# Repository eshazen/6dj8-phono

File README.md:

# 6dj8 phono preamp

This is a project to build a 6DJ8 (ECC88) tube phono stage as inspired by RJM audio (phonoclone.com).  The 6DJ8 seems to be out of production, but still readily available.

## Power board:

IEC power input, fuse, switch, neon as in https://github.com/eshazen/6cy7-amp.  PT, chokes mounted on PCB also.  Single noval socket for 6CA4 (ceramic).  Two B+ outputs for two channels.

## Channel board (2):

Single tube (6DJ8/ECC88) per channel.  RCA inputs and outputs, plus GND.  Power connector.

## Progress

*2021-05-01* - Schematics done for PS and amp.  Footprints done and DigiKey numbers on amp schematic, starting placement

*2021-05-02* - Finished amp layout, placement for PS.  Resized boards so the stack of 3 has the same footprint as the 6CY7 amp (7.5 x 15").

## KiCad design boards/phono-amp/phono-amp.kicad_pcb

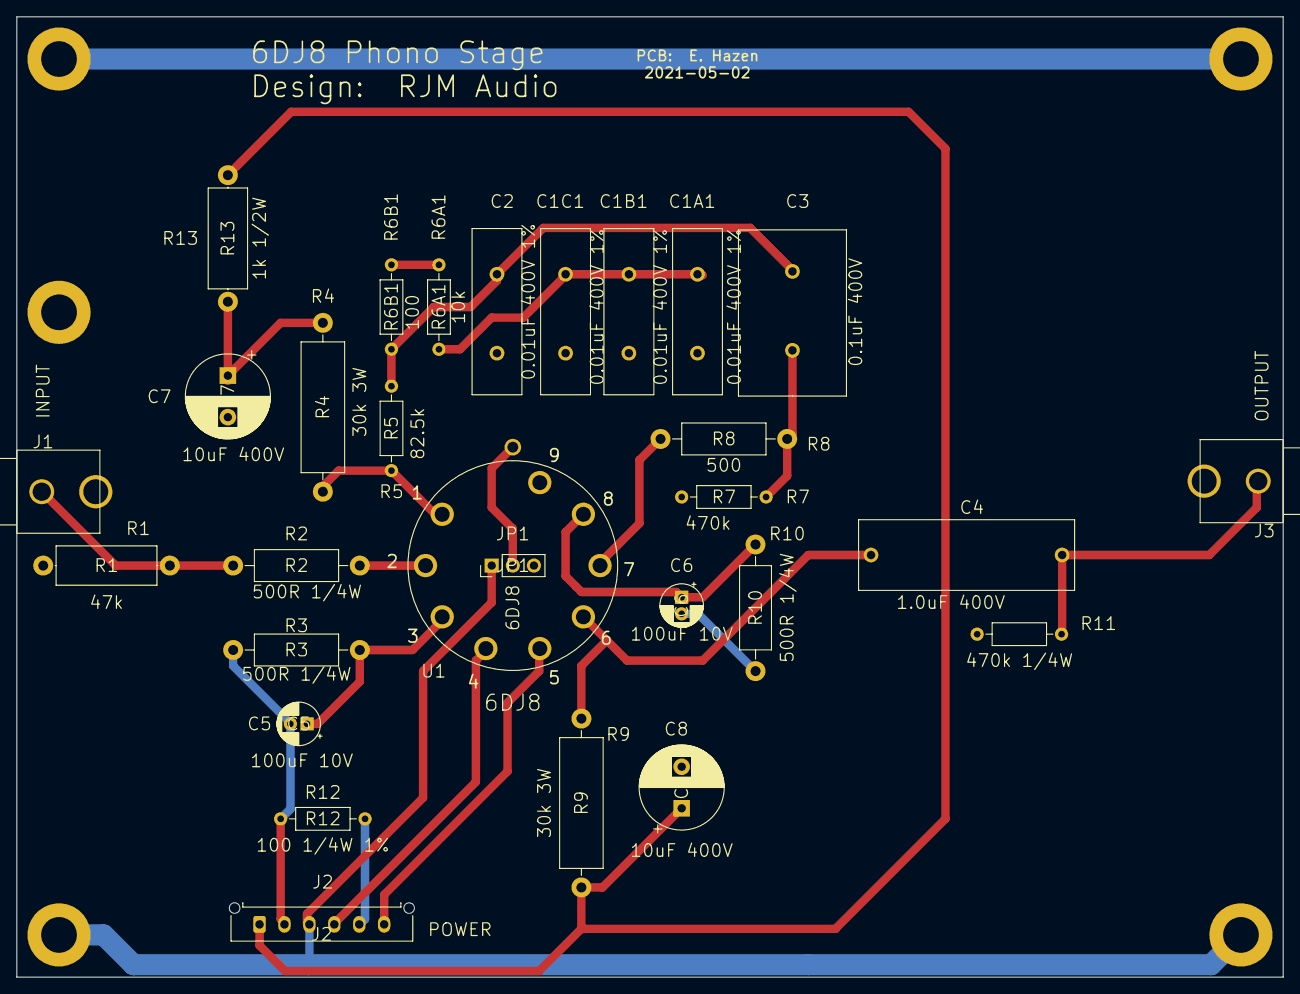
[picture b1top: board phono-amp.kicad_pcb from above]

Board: 2 copper layers, 152.4 x 115.6 mm, 34 parts (0 on the bottom side), 20 nets.

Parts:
C1A1, C1B1, C1C1, C2: 0.01uF 400V 1%; CAP_L20_W6.4_P9.5
C3: 0.1uF 400V; CAP_L20_W13_P9.5
C4: 1.0uF 400V; CAP_L26_W8.5_P22.5
C5, C6: 100uF 10V; CP_Radial_D5.0mm_P2.00mm
C7, C8: 10uF 400V; CP_Radial_D10.0mm_P5.00mm
H1, H2, H3, H4, H5: MountingHole_Pad; MountingHole_4.3mm_M4_ISO7380_Pad
J1: INPUT; rca-single-klpx
J2: POWER; Molex_Micro-Fit_3.0_43650-0615_1x06_P3.00mm_Vertical
J3: OUTPUT; rca-single-klpx
JP1: 6DJ8; PinHeader_1x03_P2.54mm_Vertical
R1: 47k; R_Axial_DIN0414_L11.9mm_D4.5mm_P15.24mm_Horizontal
R2, R3, R10: 500R 1/4W; R_Axial_DIN0411_L9.9mm_D3.6mm_P15.24mm_Horizontal
R4, R9: 30k 3W; R_Axial_DIN0516_L15.5mm_D5.0mm_P20.32mm_Horizontal
R5: 82.5k; R_Axial_DIN0207_L6.3mm_D2.5mm_P10.16mm_Horizontal
R6A1: 10k; R_Axial_DIN0207_L6.3mm_D2.5mm_P10.16mm_Horizontal
R6B1: 100; R_Axial_DIN0207_L6.3mm_D2.5mm_P10.16mm_Horizontal
R7: 470k; R_Axial_DIN0207_L6.3mm_D2.5mm_P10.16mm_Horizontal
R8: 500; R_Axial_DIN0411_L9.9mm_D3.6mm_P15.24mm_Horizontal
R11: 470k 1/4W; R_Axial_DIN0207_L6.3mm_D2.5mm_P10.16mm_Horizontal
R12: 100 1/4W 1%; R_Axial_DIN0207_L6.3mm_D2.5mm_P10.16mm_Horizontal
R13: 1k 1/2W; R_Axial_DIN0414_L11.9mm_D4.5mm_P15.24mm_Horizontal
U1: 6DJ8; P-ST9-700-PC

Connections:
Earth_Protective: H1.1, H2.1, H3.1, H4.1, J2.3, JP1.1
GND: C1A1.2, C1B1.2, C1C1.2, C2.2, C5.2, C6.2, C7.2, C8.2, H5.1, J1.2, J2.2, J3.2, JP1.3, R1.1, R3.1, R7.1, R10.1, R11.1, R12.1, U1.9
unnamed: C1A1.1, C1B1.1, C1C1.1, R6A1.1
unnamed: C2.1, C3.2, R5.1, R6B1.2
unnamed: C3.1, R7.2, R8.2
unnamed: C4.1, J3.1, R11.2
unnamed: C4.2, R9.1, U1.6
unnamed: C5.1, R3.2, U1.3
unnamed: C6.1, R10.2, U1.8
unnamed: C7.1, R4.2, R13.2
unnamed: J1.1, R1.2, R2.2
unnamed: J2.4, U1.4
unnamed: J2.5, R12.2
unnamed: J2.6, U1.5
unnamed: JP1.2, U1.10
unnamed: R2.1, U1.2
unnamed: R4.1, R5.2, U1.1
unnamed: R6A1.2, R6B1.1
unnamed: R8.1, U1.7
VBUS: C8.1, J2.1, R9.2, R13.1

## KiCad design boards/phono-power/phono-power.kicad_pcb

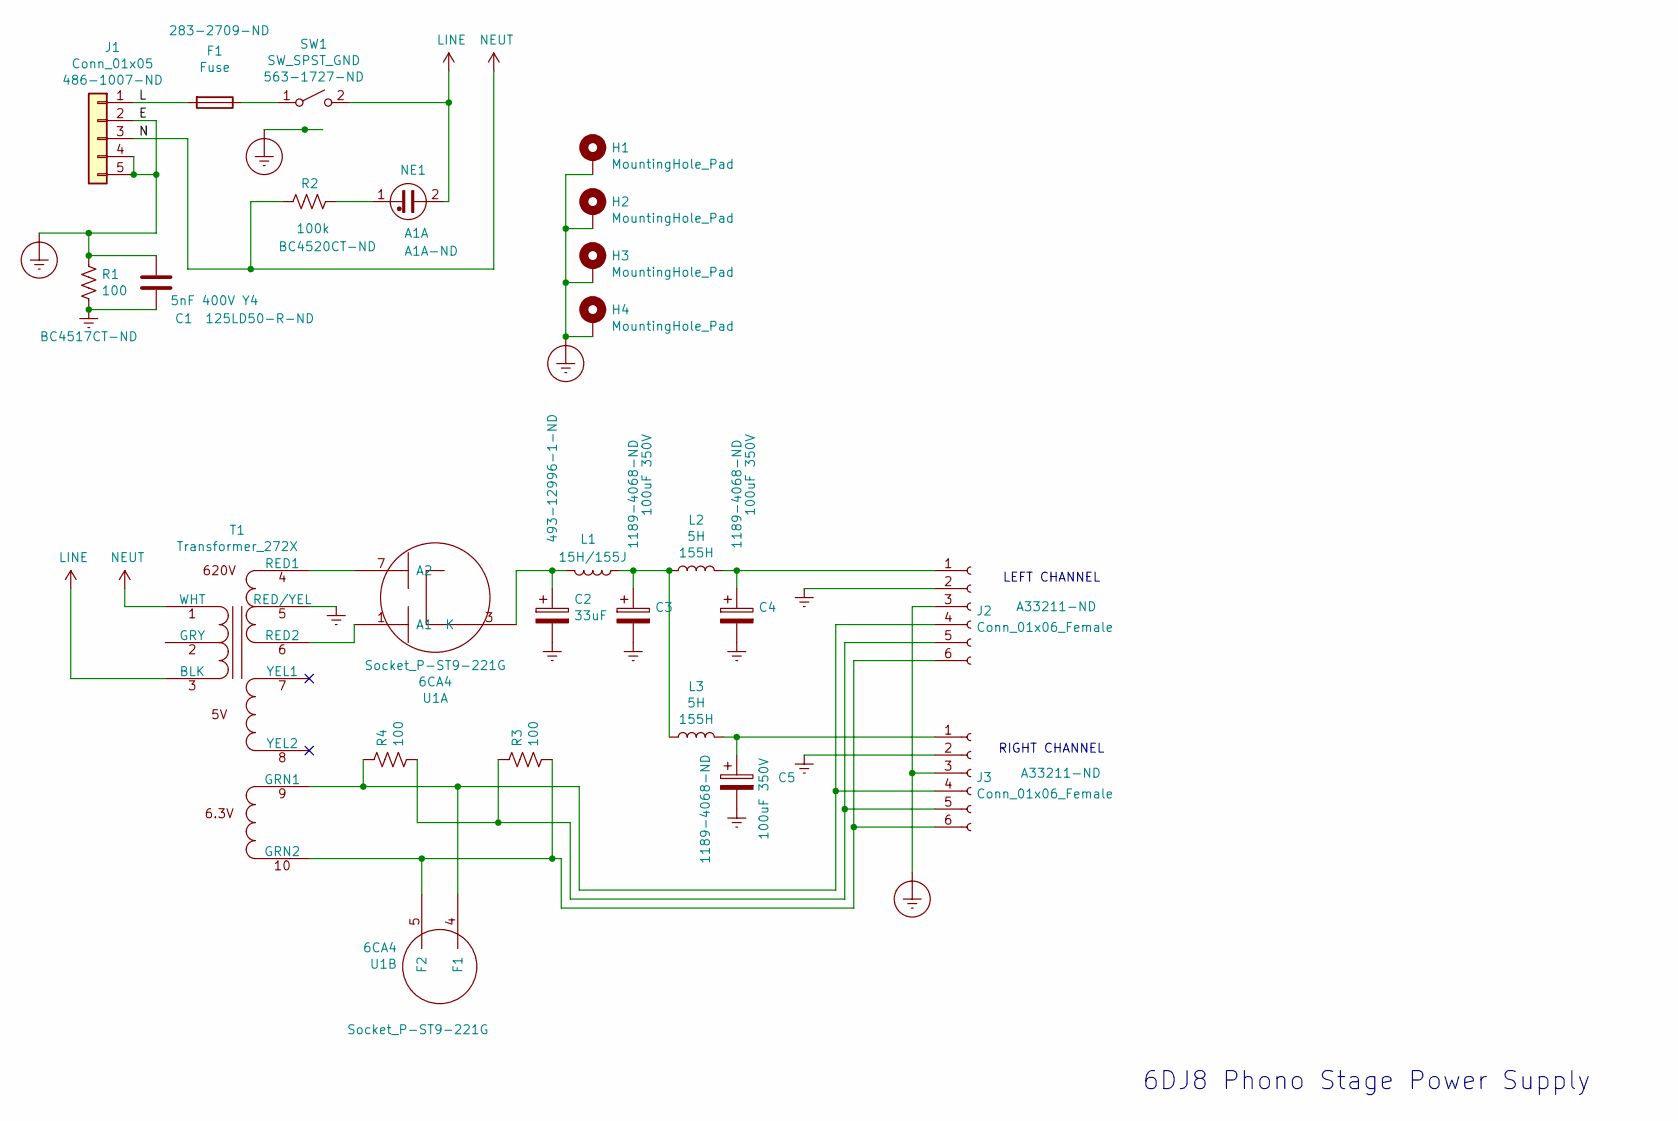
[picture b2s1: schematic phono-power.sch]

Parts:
C1: 5nF 400V Y4; C_Disc_D11.0mm_W5.0mm_P10.00mm
C2: 33uF; CP_Radial_D12.5mm_P5.00mm
C3, C4, C5: 100uF 350V; CP_Radial_D18.0mm_P7.50mm
F1: Fuse; HBH-I-R
H1, H2, H3, H4: MountingHole_Pad; Mtg6-32
J1: Conn_01x05; GSP1.8101.1
J2, J3: Conn_01x06_Female; Molex_Micro-Fit_3.0_43650-0615_1x06_P3.00mm_Vertical
L1: 15H/155J; 156L
L2, L3: 5H; 155H
NE1: A1A
R1, R3, R4: 100; R_Axial_DIN0414_L11.9mm_D4.5mm_P15.24mm_Horizontal
R2: 100k; R_Axial_DIN0414_L11.9mm_D4.5mm_P15.24mm_Horizontal
SW1: SW_SPST_GND; 8GA1016-Z
T1: Transformer_272X; Hammond-272X
U1: 6CA4; P-ST9-700-PC

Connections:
/L: F1.2, J1.1
Earth: C1.1, C2.2, C3.2, C4.2, C5.2, J2.2, J3.2, R1.2, T1.5 (RED/YEL)
Earth_Protective: C1.2, H1.1, H2.1, H3.1, H4.1, J1.2, J1.4, J1.5, J2.3, J3.3, R1.1, SW1.4 (G1), SW1.5 (G2)
LINE: NE1.2, SW1.2 (B), T1.3 (BLK)
NEUT: J1.3, R2.2, T1.1 (WHT)
unnamed: C2.1, L1.2, U1.3 (K)
unnamed: C3.1, L1.1, L2.1, L3.1
unnamed: C4.1, J2.1, L2.2
unnamed: C5.1, J3.1, L3.2
unnamed: F1.1, SW1.1 (A)
unnamed: J2.4, J3.4, R4.1, T1.9 (GRN1), U1.4 (F1)
unnamed: J2.5, J3.5, R3.1, R4.2
unnamed: J2.6, J3.6, R3.2, T1.10 (GRN2), U1.5 (F2)
unnamed: NE1.1, R2.1
unnamed: T1.4 (RED1), U1.7 (A2)
unnamed: T1.6 (RED2), U1.1 (A1)

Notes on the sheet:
6DJ8 Phono Stage Power Supply
LEFT CHANNEL
RIGHT CHANNEL

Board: 2 copper layers, 24 parts (0 on the bottom side), 16 nets, no tracks yet.

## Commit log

2021-05-01 Starting parts list
2021-05-01 First version power supply schematic
2021-05-01 amp schematic draft
2021-05-02 footprints done, starting placement
2021-05-02 layout underway
2021-05-02 Amp PCB done?
2021-05-02 Pause to consider board sizes
2021-05-02 resize boards
2022-06-06 synching up
